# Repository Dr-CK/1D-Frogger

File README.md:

# 1D-Frogger
KiCAD project files for a minimalist one dimensional game of Frogger

See BOM for components and assembly notes

How to play the game:
* Press the button while the light is green to advance Frogger until you reach the final light.
* If you press it while it's red, Frogger goes back to the starting position.
* The flashing will be faster and faster, so act quickly!
* The difficulty can be adjusted by shorting the J4 pins with a jumper (faster flashing).

CC BY-NC-SA

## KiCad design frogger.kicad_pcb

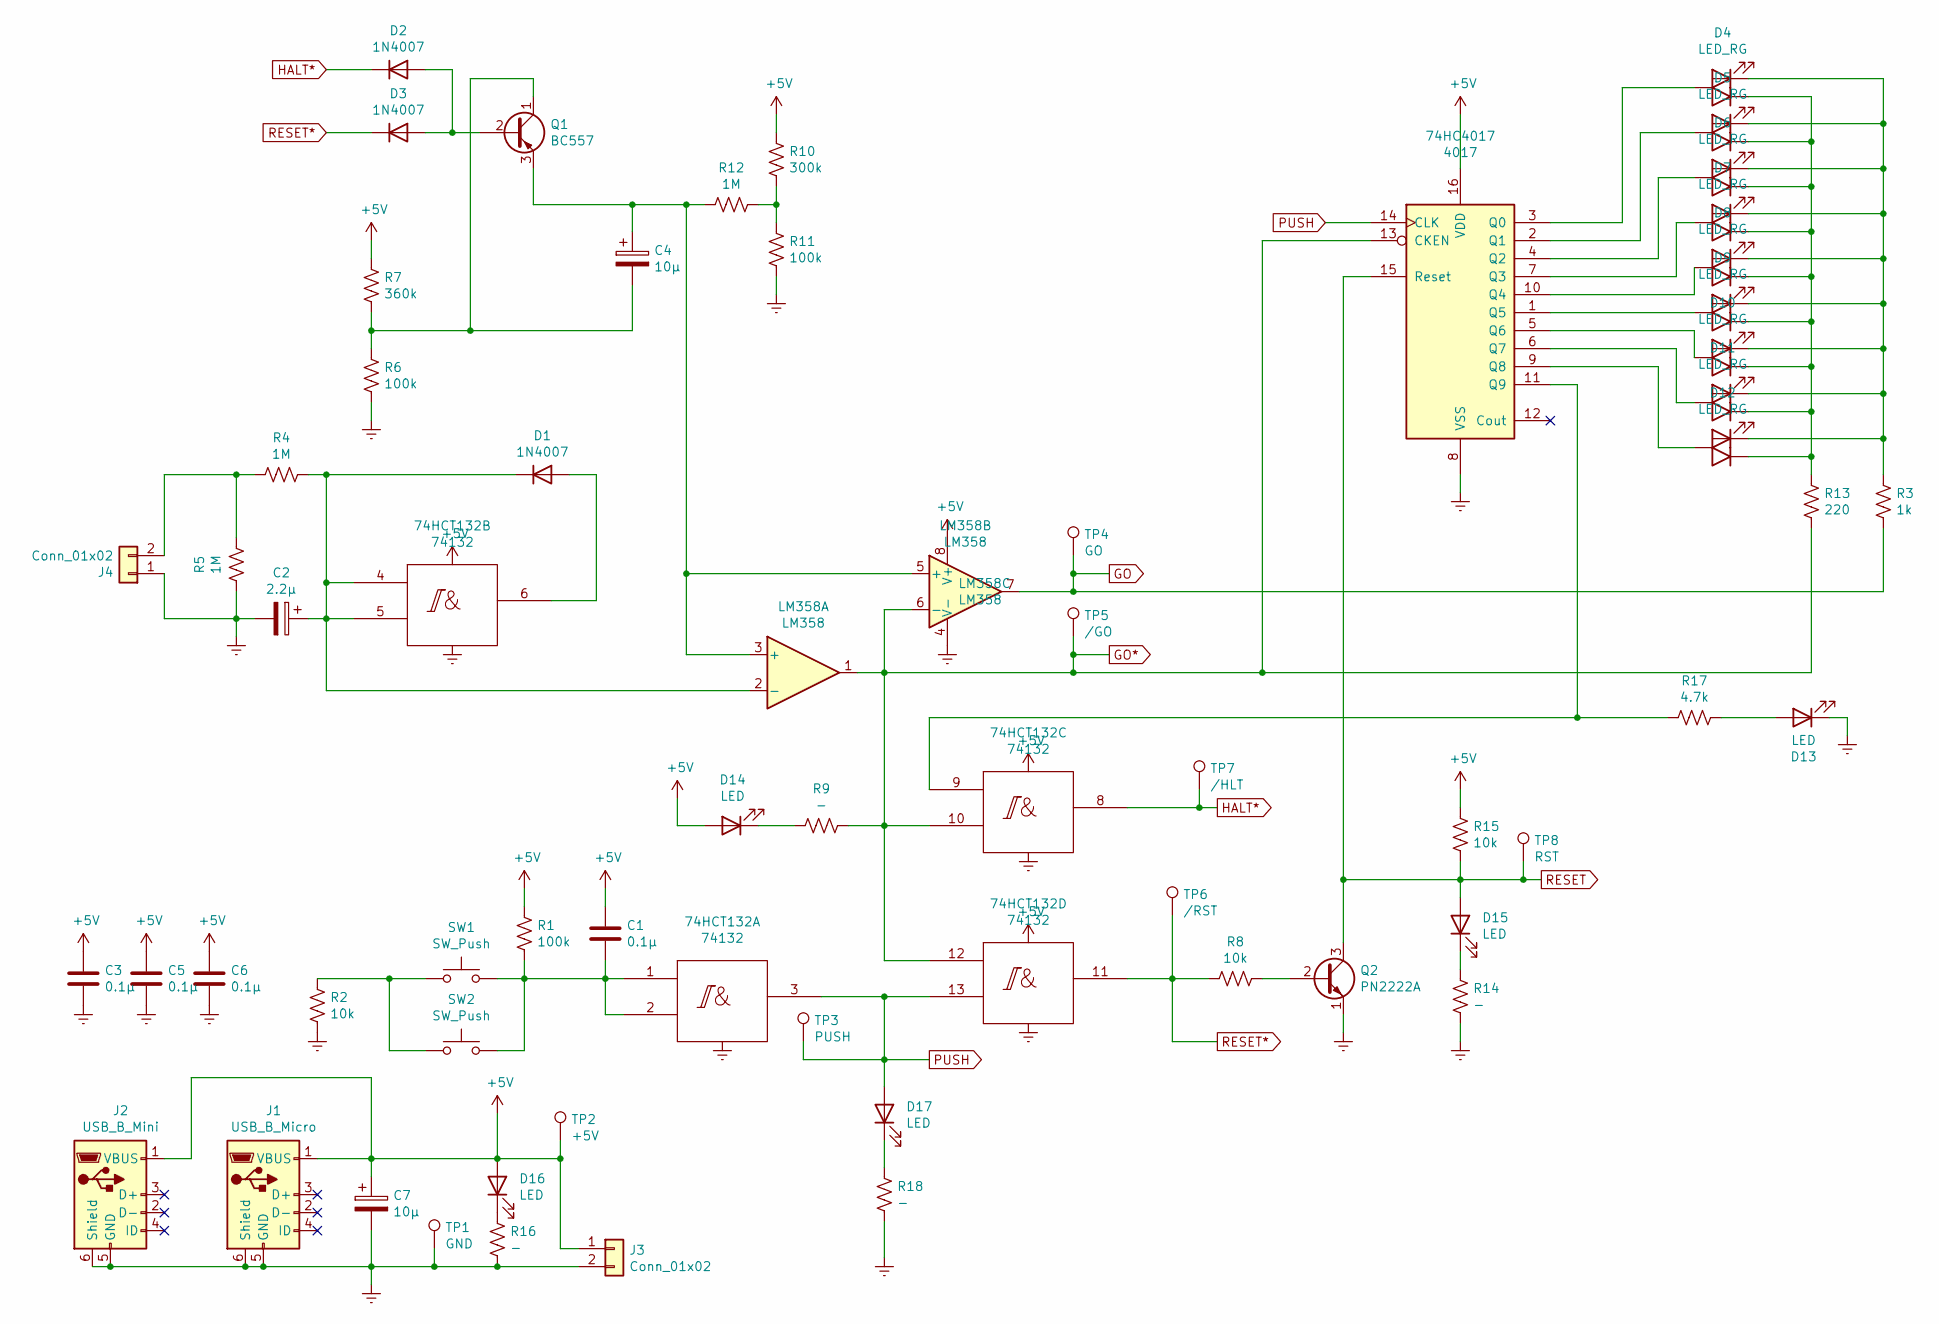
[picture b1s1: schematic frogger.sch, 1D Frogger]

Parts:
74HC4017: 4017; DIP-16_W7.62mm
74HCT132: 74132; DIP-14_W7.62mm
C1, C3, C5, C6: 0.1µ; C_Radial_D5.0mm_H7.0mm_P2.00mm
C2: 2.2µ; CP_Radial_D5.0mm_P2.50mm
C4, C7: 10µ; CP_Radial_D5.0mm_P2.50mm
D1, D2, D3: 1N4007; D_DO-41_SOD81_P10.16mm_Horizontal
D4, D5, D6, D7, D8, D9, D10, D11, D12: LED_RG; LED_D3.0mm-3
D13, D14, D15, D16, D17: LED; LED_D3.0mm
J1: USB_B_Micro; USB_Micro-B_Amphenol_10118194_Horizontal
J2: USB_B_Mini; USB_Mini-B_Lumberg_2486_01_Horizontal
J3, J4: Conn_01x02; PinHeader_1x02_P2.54mm_Vertical
LM358: LM358; DIP-8_W7.62mm
Q1: BC557; TO-92_Inline
Q2: PN2222A; TO-92_Inline
R1, R6, R11: 100k; R_Axial_DIN0207_L6.3mm_D2.5mm_P10.16mm_Horizontal
R2, R8, R15: 10k; R_Axial_DIN0207_L6.3mm_D2.5mm_P10.16mm_Horizontal
R3: 1k
R4, R5, R12: 1M; R_Axial_DIN0207_L6.3mm_D2.5mm_P10.16mm_Horizontal
R7: 360k; R_Axial_DIN0207_L6.3mm_D2.5mm_P10.16mm_Horizontal
R9, R14, R16, R18: -; R_Axial_DIN0207_L6.3mm_D2.5mm_P10.16mm_Horizontal
R10: 300k; R_Axial_DIN0207_L6.3mm_D2.5mm_P10.16mm_Horizontal
R13: 220; R_Axial_DIN0207_L6.3mm_D2.5mm_P10.16mm_Horizontal
R17: 4.7k; R_Axial_DIN0207_L6.3mm_D2.5mm_P10.16mm_Horizontal
SW1: SW_Push; SW_PUSH-12mm
SW2: SW_Push; SW_PUSH_6mm
TP1: GND; TestPoint_Pad_D3.0mm
TP2: +5V; TestPoint_Pad_D3.0mm
TP3: PUSH; TestPoint_Pad_D3.0mm
TP4: GO; TestPoint_Pad_D3.0mm
TP5: /GO; TestPoint_Pad_D3.0mm
TP6: /RST; TestPoint_Pad_D3.0mm
TP7: /HLT; TestPoint_Pad_D3.0mm
TP8: RST; TestPoint_Pad_D3.0mm

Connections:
+5V: 74HC4017.16 (VDD), 74HCT132.14 (Vcc), C1.1, C3.1, C5.1, C6.1, C7.1, D14.2 (A), D16.2 (A), J1.1 (VBUS), J2.1 (VBUS), J3.1, LM358.8 (V+), R1.1, R7.1, R10.1, R15.1, TP2.1
Earth: 74HC4017.8 (VSS), 74HCT132.7 (Gnd), C2.2, C3.2, C5.2, C6.2, C7.2, D13.1 (K), J1.5 (GND), J1.6 (Shield), J2.5 (GND), J2.6 (Shield), J3.2, J4.1, LM358.4 (V-), Q2.1 (E), R2.2, R5.2, R6.2, R11.2, R14.2, R16.2, R18.2, TP1.1
GO: LM358.7, R3.2, TP4.1
GO*: 74HC4017.13 (CKEN), 74HCT132.10, 74HCT132.12, LM358.1, LM358.6 (-), R9.1, R13.2, TP5.1
HALT*: 74HCT132.8, D2.1 (K), TP7.1
unnamed: 74HC4017.1 (Q5), D9.2 (A)
unnamed: 74HC4017.2 (Q1), D5.2 (A)
unnamed: 74HC4017.3 (Q0), D4.2 (A)
unnamed: 74HC4017.4 (Q2), D6.2 (A)
unnamed: 74HC4017.5 (Q6), D10.2 (A)
unnamed: 74HC4017.6 (Q7), D11.2 (A)
unnamed: 74HC4017.7 (Q3), D7.2 (A)
unnamed: 74HC4017.9 (Q8), D12.2 (A)
unnamed: 74HC4017.10 (Q4), D8.2 (A)
unnamed: 74HC4017.11 (Q9), 74HCT132.9, R17.2
unnamed: 74HCT132.1, 74HCT132.2, C1.2, R1.2, SW1.2, SW2.2
unnamed: 74HCT132.4, 74HCT132.5, C2.1, D1.1 (K), LM358.2 (-), R4.1
unnamed: 74HCT132.6, D1.2 (A)
unnamed: C4.1, LM358.3 (+), LM358.5 (+), Q1.3 (E), R12.2
unnamed: C4.2, Q1.1 (C), R6.1, R7.2
unnamed: D2.2 (A), D3.2 (A), Q1.2 (B)
unnamed: D4.1 (G), D5.1 (G), D6.1 (G), D7.1 (G), D8.1 (G), D9.1 (G), D10.1 (G), D11.1 (G), D12.1 (G), R13.1
unnamed: D4.3 (R), D5.3 (R), D6.3 (R), D7.3 (R), D8.3 (R), D9.3 (R), D10.3 (R), D11.3 (R), D12.3 (R), R3.1
unnamed: D13.2 (A), R17.1
unnamed: D14.1 (K), R9.2
unnamed: D15.1 (K), R14.1
unnamed: D16.1 (K), R16.1
unnamed: D17.1 (K), R18.1
unnamed: J4.2, R4.2, R5.1
unnamed: Q2.2 (B), R8.1
unnamed: R2.1, SW1.1, SW2.1
unnamed: R10.2, R11.1, R12.1
PUSH: 74HC4017.14 (CLK), 74HCT132.3, 74HCT132.13, D17.2 (A), TP3.1
RESET: 74HC4017.15 (Reset), D15.2 (A), Q2.3 (C), R15.2, TP8.1
RESET*: 74HCT132.11, D3.1 (K), R8.2, TP6.1

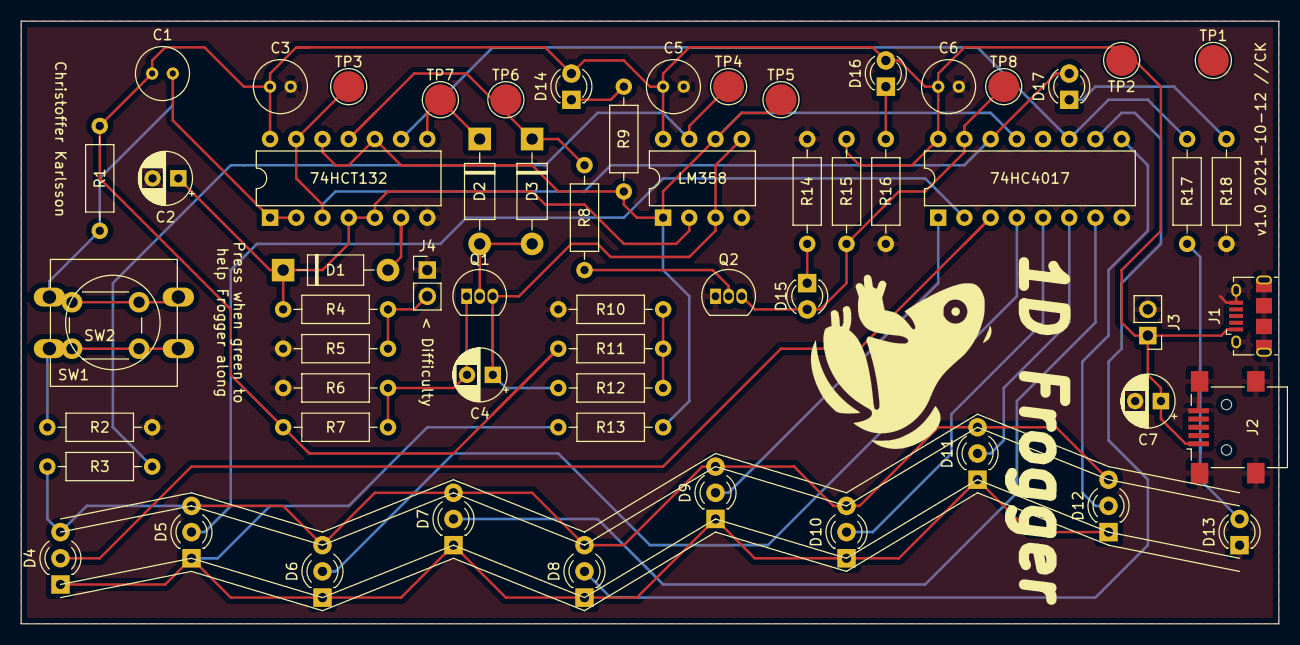
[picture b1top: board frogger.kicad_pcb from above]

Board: 2 copper layers, 121.9 x 58.4 mm, 62 parts (0 on the bottom side), 35 nets.

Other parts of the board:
ICON: FROG; frog1

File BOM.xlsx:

Frogger 1D BOM
Code | Component value | Comment
ICs
U1 | 74HC4017 | Decade counter
U2 | LM358 | Operational amplifier
U3 | 74HCT132 | Schmitt trigger quad NAND gate
Resistors
R1 | 100k
R2 | 10k
R3 | 1k | For red LEDs
R4 | 1M
R5 | 1M
R6 | 100k
R7 | 360k
R8 | 10k
R9 | N/A | *Optional (~220 ohm), for testing
R10 | 100k
R11 | 300k
R12 | 1M
R13 | 220 ohm | For green LEDs
R14 | N/A | *; Has to be >1k if used
R15 | 10k
R16 | N/A | *
R17 | 4.7k-10k | For white LED
R18 | N/A | *
Capacitors
C1 | 0.1µF ceramic
C2 | 2.2 µF electrolytic | *White = cathode; +,square = anode
C3 | 0.1µF ceramic
C4 | 10 µF electrolytic | *
C5 | 0.1µF ceramic
C6 | 0.1µF ceramic
C7 | 10 µF electrolytic | *
Diodes
D1 | 1N4001 | *Line, square = cathode
D2 | 1N4001 | *
D3 | 1N4001 | *
D4-D12 | Red/green common anode LEDs | Center = anode (longest leg); square = green (shortest leg)
D13 | White LED | **Square = cathode
D14-D17 | N/A | Optional LEDs for testing; **
Transistors |  | N.B. Pads are very close together, solder with care!
Q1 | BC557 | PNP
Q2 | PN2222 | NPN
Connectors
J1 | USB-B micro | *One power supply (J1, J2 or J3)
J2 | USB-B mini | *
J3 | Pin header power supply | Square = +5V; circle = GND; *
J4 | Pin header with jumper | Short-circuit pins for higher difficulty
Switches
SW1 | Momentary push button | *One switch (SW1 or SW2)
SW2 | Momentary push button | *
Test points
TP1 | N/A | Ground
TP2 | N/A | +5V
TP3 | N/A | PUSH
TP4 | N/A | GO
TP5 | N/A | /GO
TP6 | N/A | /RST
TP7 | N/A | /HLT

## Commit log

2021-12-03 KiCAD project
2021-12-05 KiCAD project 1.0
2021-12-05 Update license
2021-12-05 Update BOM
2021-12-07 Picture of assembled circuit board
